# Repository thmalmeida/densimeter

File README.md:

# densimeter

## Schematic

## PCB

## 3D View

## Dimension (Unit:mm)

## Pinmap

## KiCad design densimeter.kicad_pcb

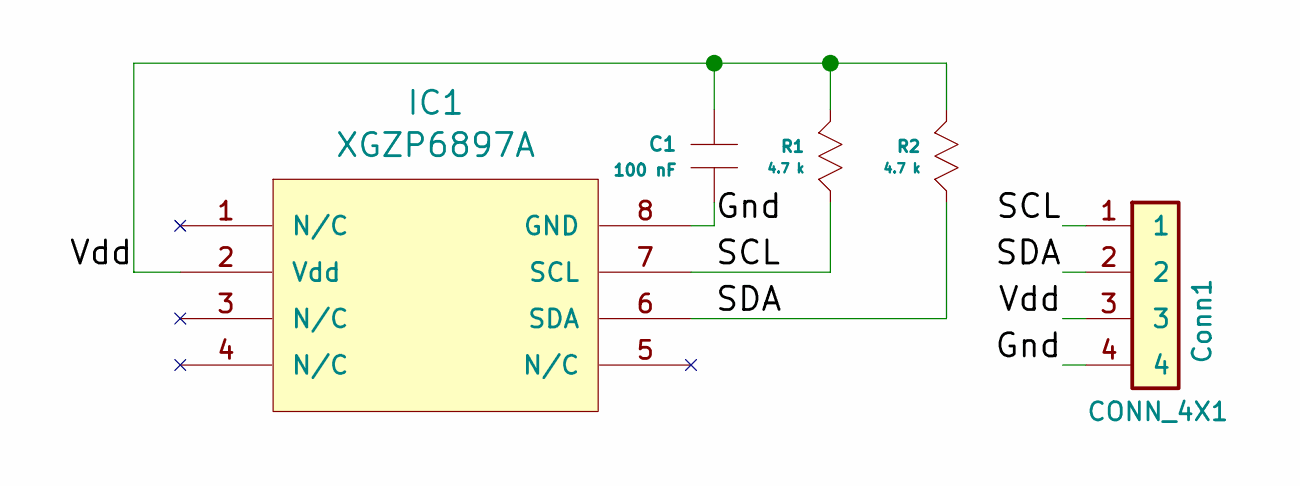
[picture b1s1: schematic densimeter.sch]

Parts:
C1: 100 nF; C_0805_2012Metric; Rated Voltage [V] xx; Tolerance [%] xx; Part Number xxxx
Conn1: CONN_4X1; PinHeader_1x04_P2.54mm_Vertical; Part Number xxxx
IC1: XGZP6897A; SMDIP-8_W9.53mm; Partnumber XGZP6897A
R1, R2: 4.7 k; R_0805_2012Metric; Tolerance [%] 5; Part Number MCT08050F1001C

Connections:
/Gnd: C1.2 (B), Conn1.4, IC1.8 (GND)
/SCL: Conn1.1, IC1.7 (SCL), R1.1 (A)
/SDA: Conn1.2, IC1.6 (SDA), R2.1 (A)
/Vdd: C1.1 (A), Conn1.3, IC1.2 (Vdd), R1.2 (B), R2.2 (B)

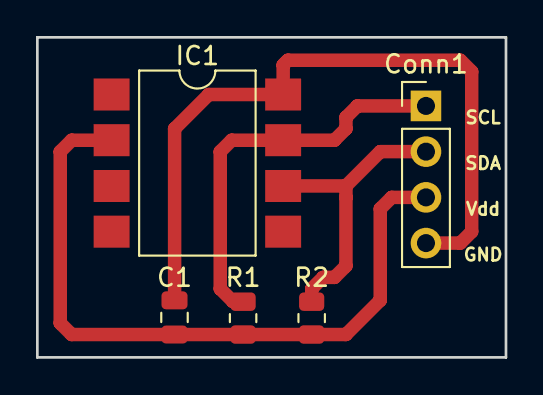
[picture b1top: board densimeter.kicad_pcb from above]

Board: 2 copper layers, 26.0 x 17.8 mm, 5 parts (0 on the bottom side), 4 nets.

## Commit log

2021-10-06 started
2021-10-06 readme doc updated
2021-10-06 added 100 nF capacitor C1
2021-10-06 4 pins module
2021-10-06 pull up resistors added
2021-10-07 pull up resistors added on images
